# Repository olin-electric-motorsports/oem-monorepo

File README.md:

<h1 align="center">
	
</h1>

Welcome to the Olin Electric Motorsports monorepo. This is the home for all of our
electrical, firmware, and software work.

This document will help you get started contributing and walk you through
important steps for working on the team.

## Getting Started

If you are on a completely fresh Ubuntu computer, you won't have the tools needed to download this repository yet. Open your terminal (`Ctrl` + `Alt` + `T`) and run these commands one by one to install Git and clone our code:

**1. Install Git:**
```shell
sudo apt update
sudo apt install git -y
git clone https://github.com/olin-electric-motorsports/oem-monorepo oem-monorepo
cd oem-monorepo
```
Now we need to install a few things so lets run. 
```shell
./scripts/startup/quick-setup.sh
```

Go through this and install the packages

## Repository Configuration

Once your system has all the required packages, you need to configure your local repository settings to keep our KiCad libraries clean.
*   Run the KiCad Git filters script to apply rules that remove temporary files and prevent clutter:
    `./scripts/startup/install_kicad_git_filters.sh`
*   Run the KiCad Git Hooks script to install Git LFS and the hooks required to generate our symbol libraries on every push/pull:
    `./scripts/startup/install_kicad_git_hooks.sh`

## Testing Your Setup

Verify that your system is ready by running the following commands in your terminal:
*   Check your Bazel installation: `bazel version`
*   Check your OpenOCD installation: `openocd --version`
*   Test the vehicle firmware build: `bazel build //vehicle/... --config=m4`

If the final command outputs a lot of green text, your environment is perfectly configured!

## Firmware Workflow

Here are the standard Bazel commands you will use to interact with the STM32 microcontrollers. 

**Building specific targets (creates the .elf file):**
`bazel build --config=m4 //vehicle/examples/blinky:blinky.elf`

**Initializing new chips (configures the boot pin on fresh silicon):**
`bazel run --config=m4 //vehicle/examples/blinky:blinky_initialize`

**Flashing firmware using the ST-Link:**
`bazel run --config=m4 //vehicle/examples/blinky:blinky_flash`

**Debugging using OpenOCD and GDB:**
`bazel run -c dbg --config=m4 //vehicle/examples/blinky:blinky_debug`

## Contributing: Branches and Pull Requests

To keep our codebase stable and functional, we do not push code directly to the `main` branch. Instead, we use branches and Pull Requests (PRs) so code can be reviewed before it is merged. Here is the standard workflow for contributing:

**1. Get the Latest Code**
Always start by making sure your local repository is up-to-date with everyone else's work:
```shell
git checkout main
git pull origin main
```

**2. Create a New Branch**
Create a new branch for your specific feature or fix. Use a descriptive name and your name so the team knows what you are working on (e.g., `CoolerJacob/blinky-led`, `Jelly_Kelly/adc-reading`):
```shell
git checkout -b your-branch-name
```

**3. Make Your Changes and Commit**
Write your code, verify it builds, and then stage and commit your changes with a clear, descriptive message:
```shell
git add .
git commit -m "Brief description of what you changed and why"
```

**4. Push Your Branch**
Upload your newly created branch to the remote repository so the team can see it:
```shell
git push -u origin your-branch-name
```

**5. Open a Pull Request (PR)**
*   Go to our repository in your web browser.
*   You will usually see a green prompt saying "Compare & pull request" for your recently pushed branch.
*   Click it, fill out a description of what your code does, and submit the PR.
*   Tag a teammate to review your code. Once it is approved, you can merge it into `main`!

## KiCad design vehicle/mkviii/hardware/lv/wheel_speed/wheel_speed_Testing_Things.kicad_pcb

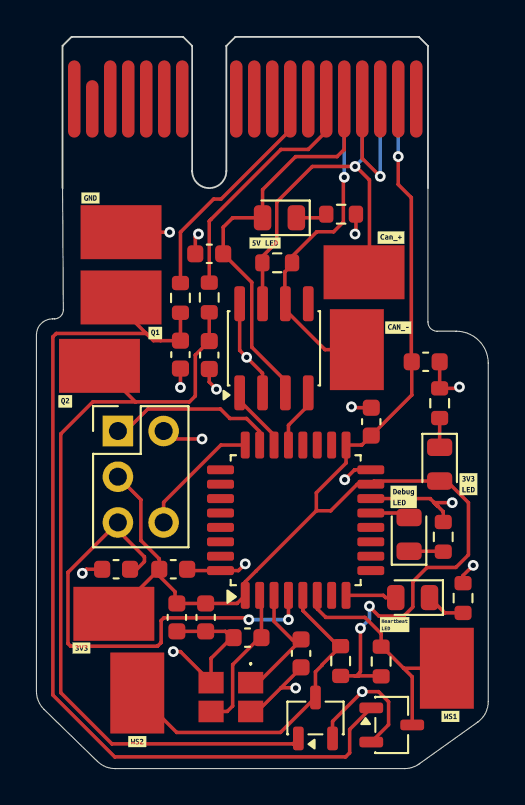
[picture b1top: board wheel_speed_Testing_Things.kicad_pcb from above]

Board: 2 copper layers, 25.1 x 40.6 mm, 51 parts (0 on the bottom side), 24 nets.

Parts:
C1, C10, C11: C_10nF; C_0603_1608Metric
C2, C3, C5, C8: C_0.1uF; C_0603_1608Metric
C4: C_1uF; C_0603_1608Metric
C6: C_4.7uF; C_0603_1608Metric
C7, C9: C_30pF; C_0603_1608Metric
Can_Testpoint1, Can_Testpoint2: TestPoint; TP_Hook_SMD
D1, D2, D3, D4: D_Blue_LED; D_0805_2012Metric
GND1: TestPoint; TP_Hook_SMD
J1: J_Programming_Pin_Header; J_Programming_Pin_Header_Keyed
J2: J_PCIe_x1; J_PCIe_x1_Key
Q1, Q2: SSM3K333R,LF; SOT-23-3
R1: R_120; R_0603_1608Metric
R2, R3, R4, R5, R7, R8, R10, R11: R_1k; R_0603_1608Metric
U1: MCP2561-E-SN; SOIC-8_3.9x4.9mm_P1.27mm
U2: STM32G441KBT6; LQFP-32_7x7mm_P0.8mm
VDD1: TestPoint; TP_Hook_SMD
WS1_Output1, WS1_Output2, WS2_Output1, WS2_Output2: TestPoint; TP_Hook_SMD
X1: X_16MHz_18pF; FA238160000MBC0 (X_16MHz_18pF_SMD - FA-238_16.0000MB-C0)
kibuzzard-6AF66A6A: G***; kibuzzard-6AF66A6A
kibuzzard-6AF66B68: G***; kibuzzard-6AF66B68
kibuzzard-6AF66B73: G***; kibuzzard-6AF66B73
kibuzzard-6AF667D2: G***; kibuzzard-6AF667D2
kibuzzard-6AF667FB: G***; kibuzzard-6AF667FB
kibuzzard-6AF6682B: G***; kibuzzard-6AF6682B
kibuzzard-6AF6683B: G***; kibuzzard-6AF6683B
kibuzzard-6AF6685D: G***; kibuzzard-6AF6685D
kibuzzard-6AF66808: G***; kibuzzard-6AF66808
kibuzzard-6AF66816: G***; kibuzzard-6AF66816
kibuzzard-6AF66821: G***; kibuzzard-6AF66821
kibuzzard-6AF66851: G***; kibuzzard-6AF66851

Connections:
+3V3: C1.1, C2.1, C3.1, C4.1, C6.1, D4.2 (A), J1.3, J2.A2 (12V/3V(DA_ONLY)), R7.1, R8.1, U2.1 (VDD), U2.15 (VDDA), U2.17 (VDD), VDD1.1
+5V: C5.2, D3.2 (A), J2.B5 (5V), U1.3 (VDD)
/CAN_+: Can_Testpoint1.1, J2.A4 (CAN+), R1.1, U1.7 (CANH)
/CAN_-: Can_Testpoint2.1, J2.A5 (CAN-), R1.2, U1.6 (CANL)
/CAN_RX: U1.4 (RXD), U2.21 ((EVENTOUT/TIM1_BKIN2/TIM1_CH4/TIM4_CH1/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)
/CAN_TX: U1.1 (TXD), U2.22 ((EVENTOUT/TIM1_ETR/TIM4_CH2/FDCAN1_TX/C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)
/DEBUG_LED: D1.2 (A), U2.13 ((EVENTOUT/UCPD1_FRSTX2/UCPD_FRSTX1/TIM1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)
/HEARTBEAT_LED: D2.2 (A), U2.8 ((EVENTOUT/SAI1_MCLK_A/LPUART1_RX/TIM15_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)
/NRST: C8.1, J1.4, U2.4 ((EVENTOUT/RCC_MCO/GPIO_EXTI10)PG10-NRST)
/SWCLK: J1.5, U2.24 ((EVENTOUT/SAI1_FS_B/USART2_TX/TIM1_BKIN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)
/SWDIO: J1.1, U2.23 ((EVENTOUT/SAI1_SD_B/TIM4_CH3/IR_OUT/I2C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)
/ws1_Vout: J2.B8 (io_5), R4.1
/ws1_fVout: Q1.3 (D), R8.2, U2.6 ((EVENTOUT/TIM15_CH1N/USART2_RTS/USART2_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), WS1_Output1.1
/ws2_Vout: J2.B6 (io_1), R5.1
/ws2_fVout: Q2.3 (D), R7.2, U2.5 ((EVENTOUT/TIM2_ETR/TIM8_ETR/TIM8_BKIN/C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), WS2_Output1.1
GND: C1.2, C2.2, C3.2, C4.2, C5.1, C6.2, C7.2, C8.2, C9.2, C10.2, C11.2, GND1.1, J1.2, J2.A3 (GND), J2.B4 (GND), Q1.2 (S), Q2.2 (S), R2.1, R3.1, R10.1, R11.1, U1.2 (VSS), U1.8 (STBY), U2.14 (VSSA), U2.16 (VSS), U2.32 (VSS), X1.2, X1.4
unnamed: D1.1 (K), R2.2
unnamed: D2.1 (K), R3.2
unnamed: D3.1 (K), R10.2
unnamed: D4.1 (K), R11.2
unnamed: C10.1, Q1.1 (G), R4.2, WS1_Output2.1
unnamed: C11.1, Q2.1 (G), R5.2, WS2_Output2.1
unnamed: C7.1, U2.3 ((EVENTOUT/SPI2_SCK)PF1-OSC_OUT), X1.1
unnamed: C9.1, U2.2 ((EVENTOUT/TIM1_CH3N/SPI2_NSS/I2C2_WS/I2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), X1.3

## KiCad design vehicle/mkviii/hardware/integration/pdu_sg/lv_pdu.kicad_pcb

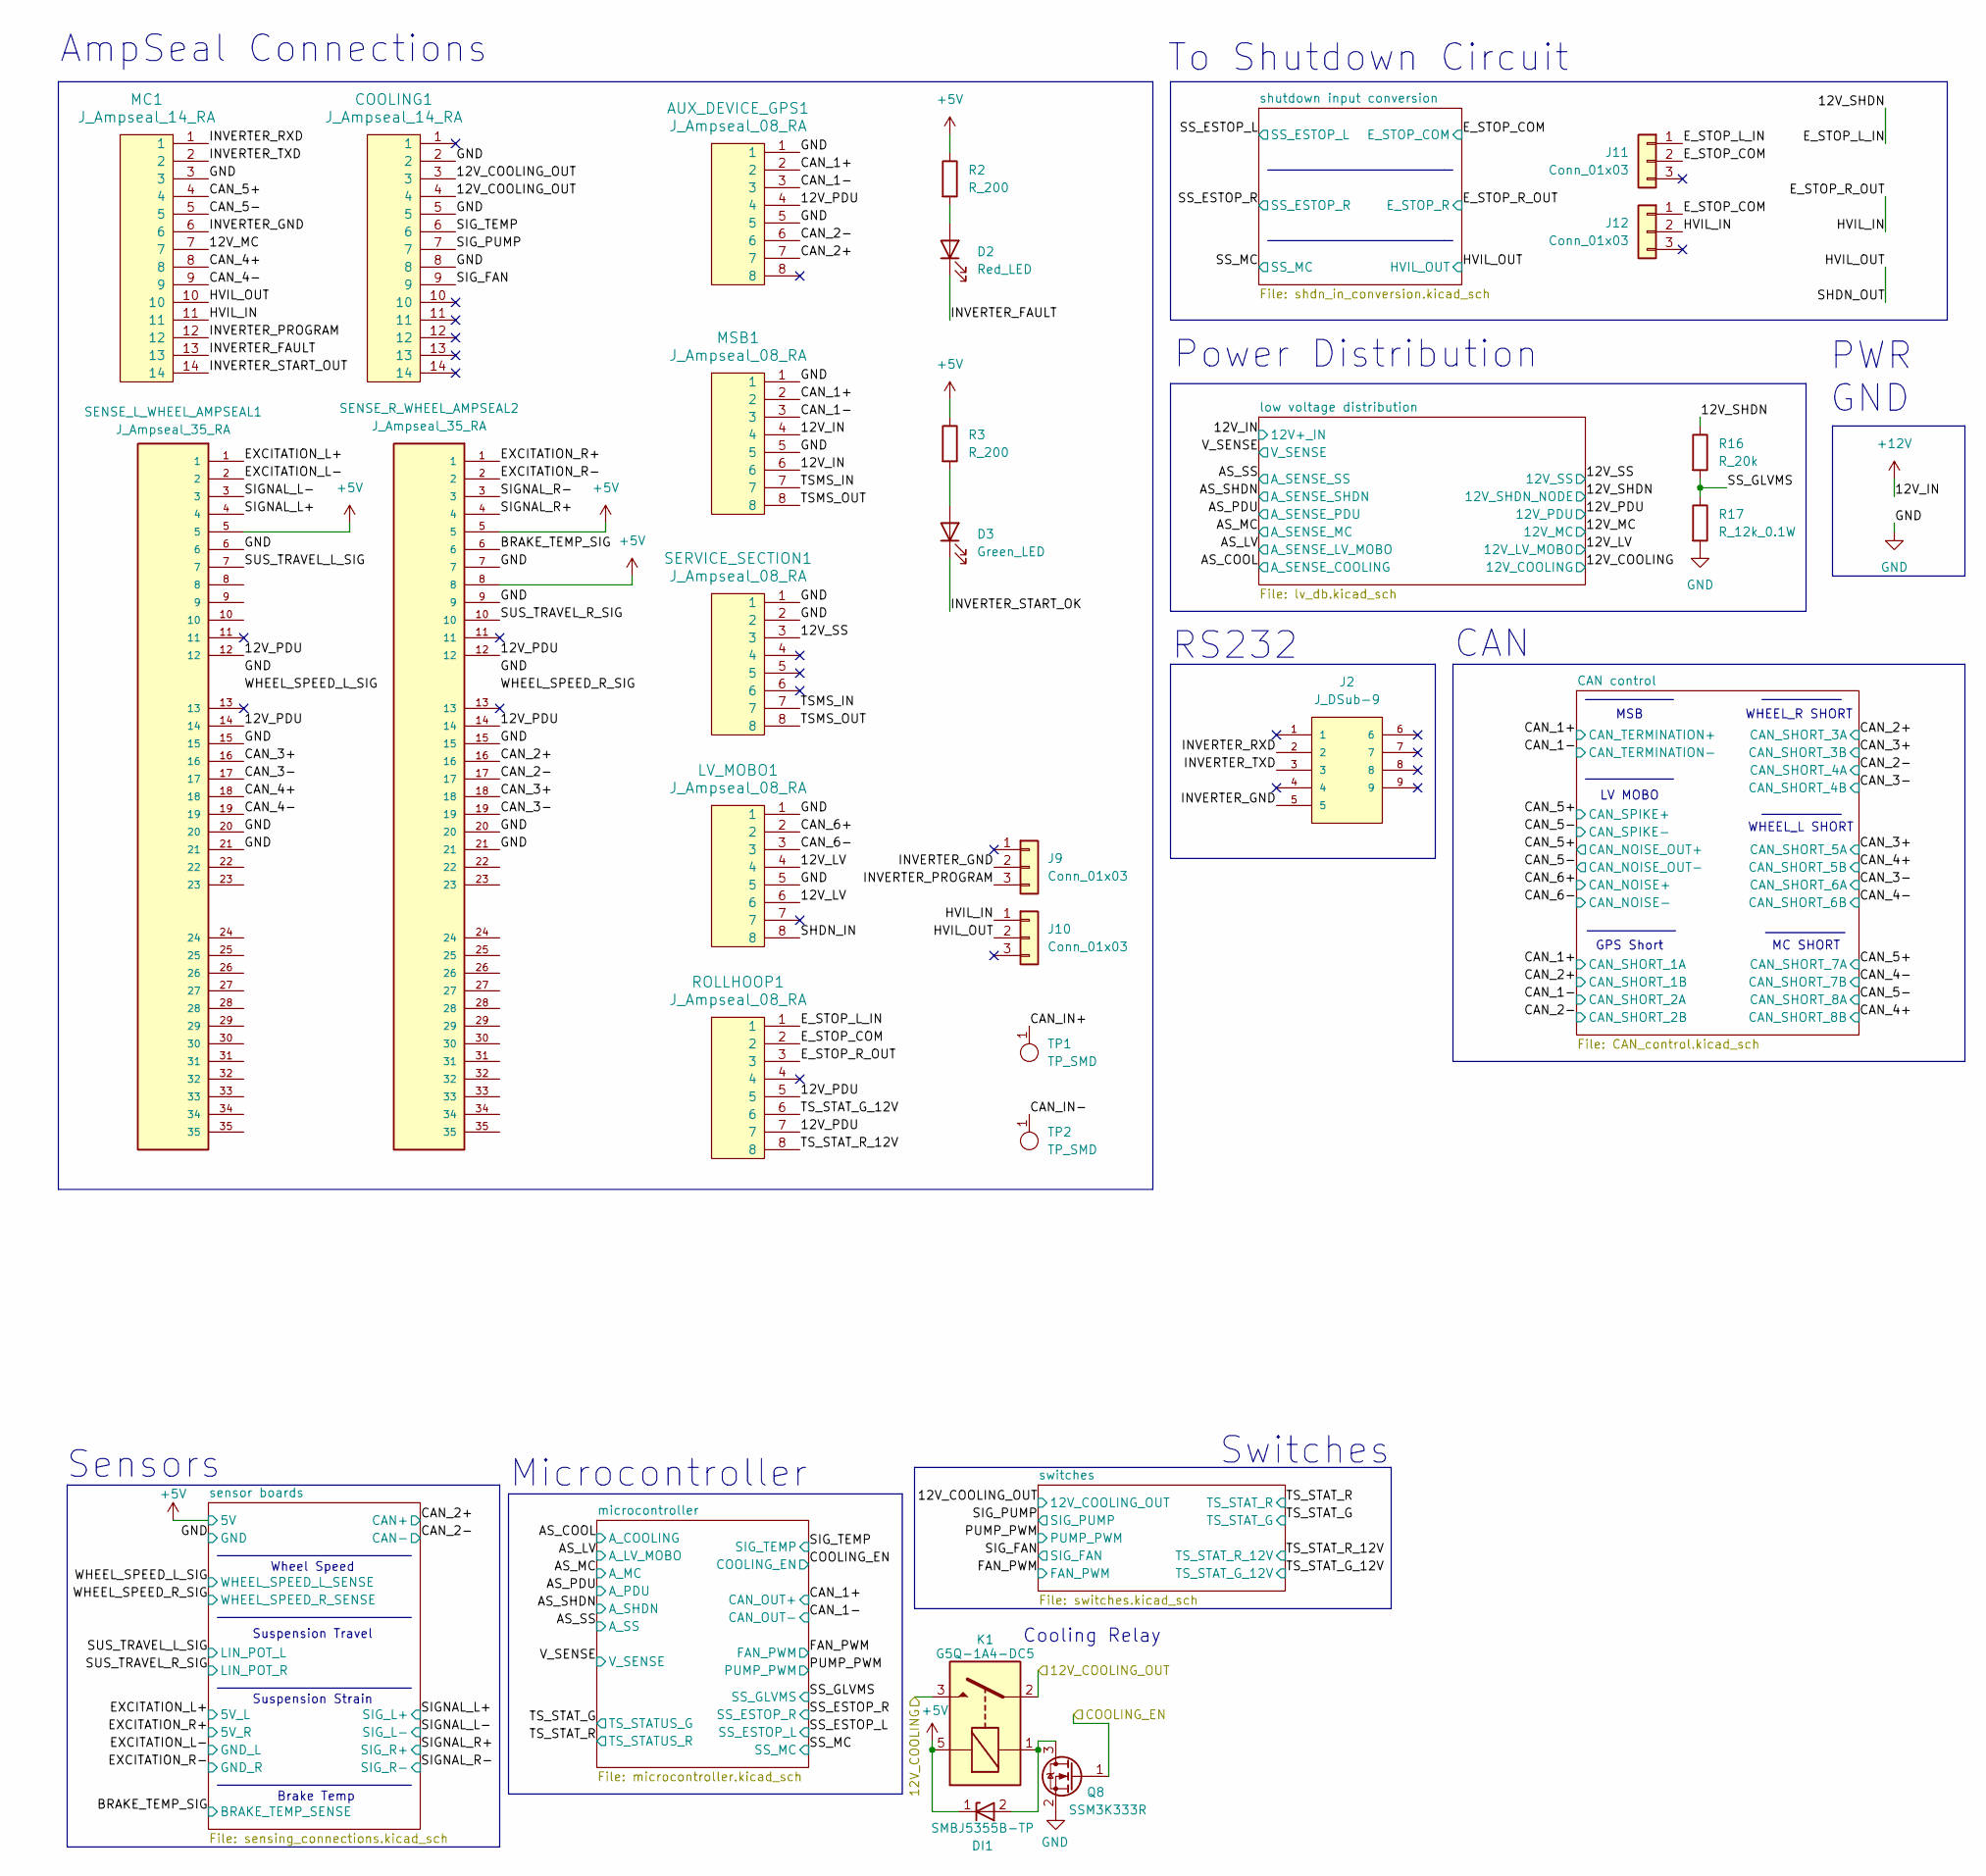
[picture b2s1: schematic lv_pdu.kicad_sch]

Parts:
AUX_DEVICE_GPS1: J_Ampseal_08_RA; J_Ampseal_8_RA; MPN 1-776279-1
COOLING1: J_Ampseal_14_RA; MPN 1-776266-1
D2: Red_LED; D_0805_2012Metric; MPN LTST-C171KRKT
D3: Green_LED; D_0805_2012Metric; MPN LTST-C170KGKT
DI1: SMBJ5355B-TP; D_Zener_18V_5W_DO214AA - DIOM5336X262N; MPN SMBJ5355B-TP
J2: J_DSub-9; J_DE-9_RA; MPN 5745781-4
J9, J10, J11, J12: Conn_01x03; PinHeader_1x03_P2.54mm_Vertical
K1: G5Q-1A4-DC5; G5Q1A4DC24 (K_SPST-NO_10A_12V_TH - G5Q-1A4-DC12); MPN G5Q-1A4 DC5
LV_MOBO1: J_Ampseal_08_RA; J_Ampseal_8_RA; MPN 1-776279-1
MC1: J_Ampseal_14_RA; MPN 1-776266-1
MSB1: J_Ampseal_08_RA; J_Ampseal_8_RA; MPN 1-776279-1
Q8: SSM3K333R; SOT-23-3; MPN SSM3K333R,LF
R2, R3: R_200; R_0603_1608Metric; MPN WR06X2000FTL
R16: R_20k; R_2512_6332Metric; MPN SR2512JK-7W20KL
R17: R_12k_0.1W; R_0603_1608Metric; MPN RMCF0603FT12K0
ROLLHOOP1: J_Ampseal_08_RA; J_Ampseal_8_RA; MPN 1-776279-1
SENSE_L_WHEEL_AMPSEAL1: J_Ampseal_35_RA; VOLTAGE_RATING 250VAC; MPN 1-776163-4
SENSE_R_WHEEL_AMPSEAL2: J_Ampseal_35_RA; VOLTAGE_RATING 250VAC; MPN 1-776163-4
SERVICE_SECTION1: J_Ampseal_08_RA; J_Ampseal_8_RA; MPN 1-776279-1
TP1, TP2: TP_SMD; TP_Hook_SMD; MPN 5019

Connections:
+5V: DI1.1 (K), K1.5, R2.1, R3.1, SENSE_L_WHEEL_AMPSEAL1.5, SENSE_R_WHEEL_AMPSEAL2.5, SENSE_R_WHEEL_AMPSEAL2.8; also elsewhere on the board
+12V: MSB1.4, MSB1.6; also elsewhere on the board
/12V_COOLING: K1.3; also elsewhere on the board
/12V_COOLING_OUT: COOLING1.3, COOLING1.4, K1.2; also elsewhere on the board
/12V_LV: LV_MOBO1.4, LV_MOBO1.6; also elsewhere on the board
/12V_MC: MC1.7; also elsewhere on the board
/12V_SHDN: J11.1, R16.1, ROLLHOOP1.1; also elsewhere on the board
/12V_SS: SERVICE_SECTION1.3; also elsewhere on the board
/BRAKE_TEMP_SIG: SENSE_R_WHEEL_AMPSEAL2.6; also elsewhere on the board
/CAN_1+: AUX_DEVICE_GPS1.2, MSB1.2; also elsewhere on the board
/CAN_1-: AUX_DEVICE_GPS1.3, MSB1.3; also elsewhere on the board
/CAN_2+: AUX_DEVICE_GPS1.7, SENSE_R_WHEEL_AMPSEAL2.16; also elsewhere on the board
/CAN_2-: AUX_DEVICE_GPS1.6, SENSE_R_WHEEL_AMPSEAL2.17; also elsewhere on the board
/CAN_3+: SENSE_L_WHEEL_AMPSEAL1.16, SENSE_R_WHEEL_AMPSEAL2.18; also elsewhere on the board
/CAN_3-: SENSE_L_WHEEL_AMPSEAL1.17, SENSE_R_WHEEL_AMPSEAL2.19; also elsewhere on the board
/CAN_4+: MC1.8, SENSE_L_WHEEL_AMPSEAL1.18; also elsewhere on the board
/CAN_4-: MC1.9, SENSE_L_WHEEL_AMPSEAL1.19; also elsewhere on the board
/CAN_5+: MC1.4; also elsewhere on the board
/CAN_5-: MC1.5; also elsewhere on the board
/CAN_6+: LV_MOBO1.2; also elsewhere on the board
/CAN_6-: LV_MOBO1.3; also elsewhere on the board
/CAN_IN+: TP1.1
/CAN_IN-: TP2.1
/COOLING_EN: Q8.1 (G); also elsewhere on the board
/EXCITATION_L+: SENSE_L_WHEEL_AMPSEAL1.1; also elsewhere on the board
/EXCITATION_L-: SENSE_L_WHEEL_AMPSEAL1.2; also elsewhere on the board
/EXCITATION_R+: SENSE_R_WHEEL_AMPSEAL2.1; also elsewhere on the board
/EXCITATION_R-: SENSE_R_WHEEL_AMPSEAL2.2; also elsewhere on the board
/E_STOP_COM: J11.2, J12.1, ROLLHOOP1.2; also elsewhere on the board
/E_STOP_R_OUT: J10.1, J12.2, MC1.11, ROLLHOOP1.3; also elsewhere on the board
/HVIL_OUT: J10.2, MC1.10; also elsewhere on the board
/INVERTER_FAULT: D2.1 (K), MC1.13
/INVERTER_GND: J2.5, J9.2, MC1.6
/INVERTER_PROGRAM: J9.3, MC1.12
/INVERTER_RXD: J2.2, MC1.1
/INVERTER_START_OK: D3.1 (K)
/INVERTER_START_OUT: MC1.14
/INVERTER_TXD: J2.3, MC1.2
/SHDN_IN: LV_MOBO1.8
/SIGNAL_L+: SENSE_L_WHEEL_AMPSEAL1.4; also elsewhere on the board
/SIGNAL_L-: SENSE_L_WHEEL_AMPSEAL1.3; also elsewhere on the board
/SIGNAL_R+: SENSE_R_WHEEL_AMPSEAL2.4; also elsewhere on the board
/SIGNAL_R-: SENSE_R_WHEEL_AMPSEAL2.3; also elsewhere on the board
/SIG_FAN: COOLING1.9; also elsewhere on the board
/SIG_PUMP: COOLING1.7; also elsewhere on the board
/SIG_TEMP: COOLING1.6; also elsewhere on the board
/SS_GLVMS: R16.2, R17.1; also elsewhere on the board
/SUS_TRAVEL_L_SIG: SENSE_L_WHEEL_AMPSEAL1.7; also elsewhere on the board
/SUS_TRAVEL_R_SIG: SENSE_R_WHEEL_AMPSEAL2.10; also elsewhere on the board
/TSMS_IN: MSB1.7, SERVICE_SECTION1.7
/TSMS_OUT: MSB1.8, SERVICE_SECTION1.8
/TS_STAT_G_12V: ROLLHOOP1.6; also elsewhere on the board
/TS_STAT_R_12V: ROLLHOOP1.8; also elsewhere on the board
GND: AUX_DEVICE_GPS1.1, AUX_DEVICE_GPS1.5, COOLING1.2, COOLING1.5, COOLING1.8, LV_MOBO1.1, LV_MOBO1.5, MC1.3, MSB1.1, MSB1.5, Q8.2 (S), R17.2, SENSE_L_WHEEL_AMPSEAL1.6, SENSE_L_WHEEL_AMPSEAL1.15, SENSE_L_WHEEL_AMPSEAL1.20, SENSE_L_WHEEL_AMPSEAL1.21, SENSE_R_WHEEL_AMPSEAL2.7, SENSE_R_WHEEL_AMPSEAL2.9, SENSE_R_WHEEL_AMPSEAL2.15, SENSE_R_WHEEL_AMPSEAL2.20, SENSE_R_WHEEL_AMPSEAL2.21, SERVICE_SECTION1.1, SERVICE_SECTION1.2; also elsewhere on the board
unnamed: D2.2 (A), R2.2
unnamed: D3.2 (A), R3.2
unnamed: DI1.2 (A), K1.1, Q8.3 (D)

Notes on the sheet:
Wheel Speed
Sensors
Switches
Suspension Travel
Power Distribution
GPS Short
Microcontroller
MSB
MC SHORT
CAN
WHEEL_R SHORT
RS232
Cooling Relay
To Shutdown Circuit
WHEEL_L SHORT
Suspension Strain
AmpSeal Connections
Brake Temp
PWR GND
LV MOBO

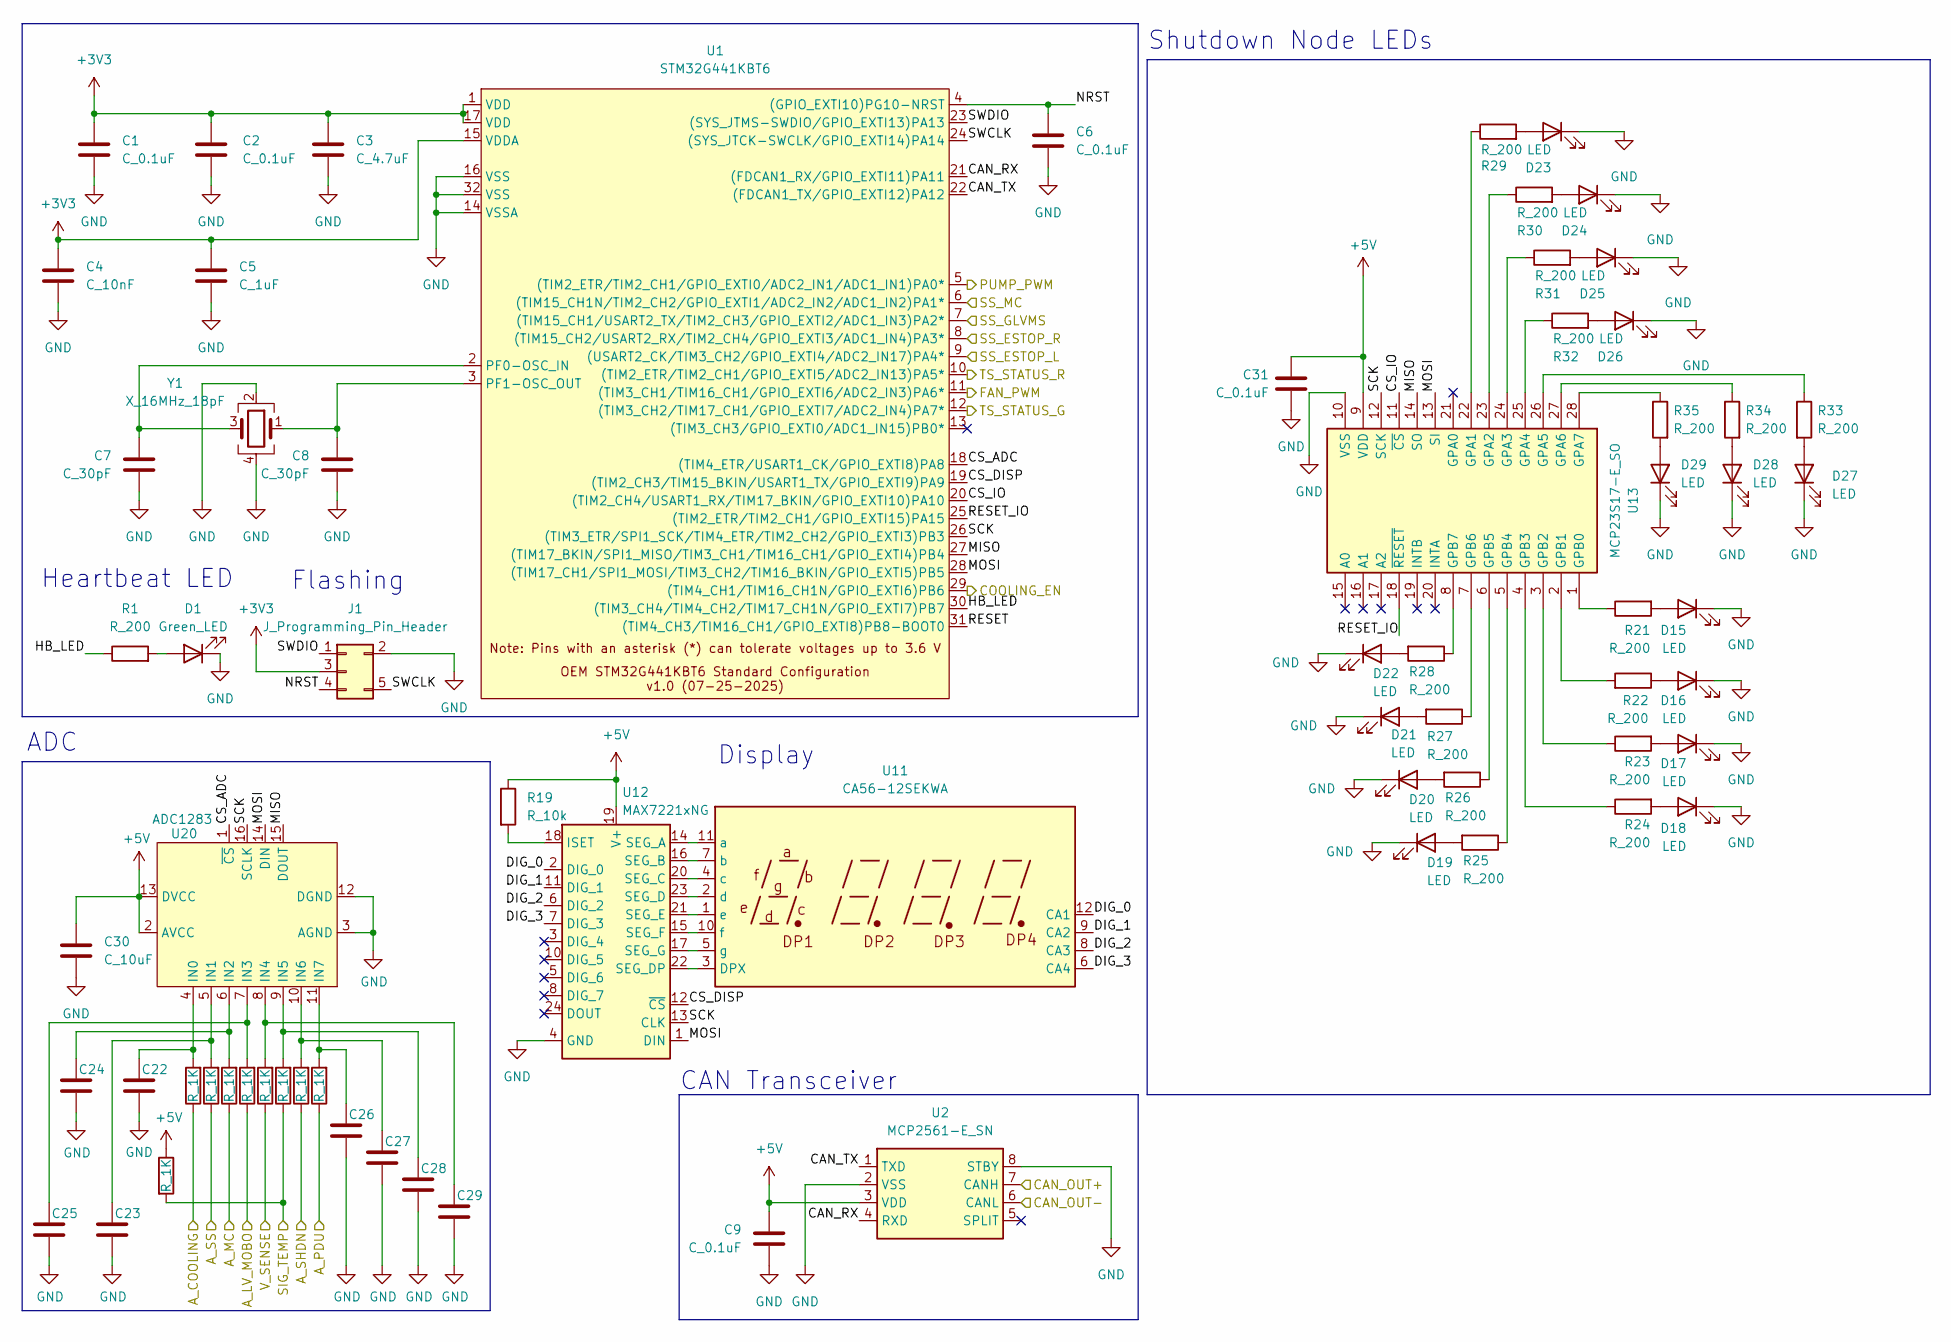
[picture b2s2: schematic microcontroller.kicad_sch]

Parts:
C1, C2, C6, C9: C_0.1uF; C_0603_1608Metric; MPN CL10B104KB8NNWC
C3: C_4.7uF; C_0603_1608Metric; MPN GRT188R61E475ME13D
C4: C_10nF; C_0603_1608Metric; MPN CL10B103KB8NNNC
C5: C_1uF; C_0603_1608Metric; MPN CL10B105KA8NNNC
C7, C8: C_30pF; C_0603_1608Metric; MPN CML0603C0G300JT50V
C22, C23, C24, C25, C26, C27, C28, C29: C_10uF; C_0603_1608Metric; MPN LMK107BBJ106KALT
C30: C_10uF; C_0603_1608Metric; MPN GRM188D71A106KA73D
C31: C_0.1uF; C_0603_1608Metric; MPN C0603C104Z4VACTU
D1: Green_LED; D_0805_2012Metric; MPN LTST-C170KGKT
D15, D16, D17, D18, D19, D20, D21, D22, D23, D24, D25, D26, D27, D28, D29: LED; D_0805_2012Metric; MPN QBLP631-IW
J1: J_Programming_Pin_Header; J_Programming_Pin_Header_Keyed
R1, R21, R22, R23, R24, R25, R26, R27, R28, R29, R30, R31, R32, R33, R34, R35: R_200; R_0603_1608Metric; MPN WR06X2000FTL
R18, R20, R45, R54, R55, R56, R57, R58, R59: R_1K; R_0603_1608Metric; MPN RMCF0603FT1K00
R19: R_10k; R_0603_1608Metric; MPN RMCF0603FT10K0
U1: STM32G441KBT6; LQFP-32_7x7mm_P0.8mm
U2: MCP2561-E_SN; SOIC-8_3.9x4.9mm_P1.27mm; MPN MCP2561-E/SN
U11: CA56-12SEKWA
U12: MAX7221xNG; DIP-24_W7.62mm
U13: MCP23S17-E_SO; U_SPI-IO-Xpndr_MCP23S17-E_SO_SOIC-28; MPN MCP23S17-E/SO
U20: ADC1283; TSSOP-16_4.4x5mm_P0.65mm
Y1: X_16MHz_18pF; FA238160000MBC0 (X_16MHz_18pF_SMD - FA-238_16.0000MB-C0); MPN FA-238 16.0000MB-C0

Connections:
+3V3: C1.1, C2.1, C3.1, C4.1, C5.1, J1.3, U1.1 (VDD), U1.15 (VDDA), U1.17 (VDD)
+5V: C9.1, C30.1, C31.1, R19.1, R45.1, U2.3 (VDD), U12.19 (V+), U13.9 (VDD), U20.2 (AVCC), U20.13 (DVCC); also elsewhere on the board
/AS_COOL: R18.1; also elsewhere on the board
/AS_LV: R55.1; also elsewhere on the board
/AS_MC: R54.1; also elsewhere on the board
/AS_PDU: R59.1; also elsewhere on the board
/AS_SHDN: R58.1; also elsewhere on the board
/AS_SS: R20.1; also elsewhere on the board
/CAN_1+: U2.7 (CANH); also elsewhere on the board
/CAN_1-: U2.6 (CANL); also elsewhere on the board
/COOLING_EN: U1.29 ((TIM4_CH1/TIM16_CH1N/GPIO_EXTI6)PB6); also elsewhere on the board
/FAN_PWM: U1.11 ((TIM3_CH1/TIM16_CH1/GPIO_EXTI6/ADC2_IN3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); also elsewhere on the board
/PUMP_PWM: U1.5 ((TIM2_ETR/TIM2_CH1/GPIO_EXTI0/ADC2_IN1/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); also elsewhere on the board
/SIG_TEMP: R45.2, R57.1; also elsewhere on the board
/SS_ESTOP_L: U1.9 ((USART2_CK/TIM3_CH2/GPIO_EXTI4/ADC2_IN1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); also elsewhere on the board
/SS_ESTOP_R: U1.8 ((TIM15_CH2/USART2_RX/TIM2_CH4/GPIO_EXTI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); also elsewhere on the board
/SS_GLVMS: U1.7 ((TIM15_CH1/USART2_TX/TIM2_CH3/GPIO_EXTI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); also elsewhere on the board
/SS_MC: U1.6 ((TIM15_CH1N/TIM2_CH2/GPIO_EXTI1/ADC2_IN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); also elsewhere on the board
/TS_STAT_G: U1.12 ((TIM3_CH2/TIM17_CH1/GPIO_EXTI7/ADC2_IN4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); also elsewhere on the board
/TS_STAT_R: U1.10 ((TIM2_ETR/TIM2_CH1/GPIO_EXTI5/ADC2_IN13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); also elsewhere on the board
/V_SENSE: R56.1; also elsewhere on the board
/microcontroller/CAN_RX: U1.21 ((FDCAN1_RX/GPIO_EXTI11)PA11), U2.4 (RXD)
/microcontroller/CAN_TX: U1.22 ((FDCAN1_TX/GPIO_EXTI12)PA12), U2.1 (TXD)
/microcontroller/CS_ADC: U1.18 ((TIM4_ETR/USART1_CK/GPIO_EXTI8)PA8), U20.1 (~CS)
/microcontroller/CS_DISP: U1.19 ((TIM2_CH3/TIM15_BKIN/USART1_TX/GPIO_EXT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), U12.12 (~CS)
/microcontroller/CS_IO: U1.20 ((TIM2_CH4/USART1_RX/TIM17_BKIN/GPIO_EXT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), U13.11 (~CS)
/microcontroller/DIG_0: U11.12 (CA1), U12.2 (DIG_0)
/microcontroller/DIG_1: U11.9 (CA2), U12.11 (DIG_1)
/microcontroller/DIG_2: U11.8 (CA3), U12.6 (DIG_2)
/microcontroller/DIG_3: U11.6 (CA4), U12.7 (DIG_3)
/microcontroller/HB_LED: R1.1, U1.30 ((TIM3_CH4/TIM4_CH2/TIM17_CH1N/GPIO_EXTI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)
/microcontroller/MISO: U1.27 ((TIM17_BKIN/SPI1_MISO/TIM3_CH1/TIM16_CH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), U13.14 (SO), U20.15 (DOUT)
/microcontroller/MOSI: U1.28 ((TIM17_CH1/SPI1_MOSI/TIM3_CH2/TIM16_BKI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), U12.1 (DIN), U13.13 (SI), U20.14 (DIN)
/microcontroller/NRST: C6.1, J1.4, U1.4 ((GPIO_EXTI10)PG10-NRST)
/microcontroller/RESET: U1.31 ((TIM4_CH3/TIM16_CH1/GPIO_EXTI8)PB8-BOOT0)
/microcontroller/RESET_IO: U1.25 ((TIM2_ETR/TIM2_CH1/GPIO_EXTI15)PA15), U13.18 (~RESET)
/microcontroller/SCK: U1.26 ((TIM3_ETR/SPI1_SCK/TIM4_ETR/TIM2_CH2/GP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), U12.13 (CLK), U13.12 (SCK), U20.16 (SCLK)
/microcontroller/SWCLK: J1.5, U1.24 ((SYS_JTCK-SWCLK/GPIO_EXTI14)PA14)
/microcontroller/SWDIO: J1.1, U1.23 ((SYS_JTMS-SWDIO/GPIO_EXTI13)PA13)
GND: C1.2, C2.2, C3.2, C4.2, C5.2, C6.2, C7.2, C8.2, C9.2, C22.2, C23.2, C24.2, C25.2, C26.2, C27.2, C28.2, C29.2, C30.2, C31.2, D1.1 (K), D15.1 (K), D16.1 (K), D17.1 (K), D18.1 (K), D19.1 (K), D20.1 (K), D21.1 (K), D22.1 (K), D23.1 (K), D24.1 (K), D25.1 (K), D26.1 (K), D27.1 (K), D28.1 (K), D29.1 (K), J1.2, U1.14 (VSSA), U1.16 (VSS), U1.32 (VSS), U2.2 (VSS), U2.8 (STBY), U12.4 (GND), U13.10 (VSS), U20.3 (AGND), U20.12 (DGND), Y1.2, Y1.4; also elsewhere on the board
unnamed: D1.2 (A), R1.2
unnamed: D15.2 (A), R21.2
unnamed: D16.2 (A), R22.1
unnamed: D17.2 (A), R23.2
unnamed: D18.2 (A), R24.2
unnamed: D19.2 (A), R25.2
unnamed: D20.2 (A), R26.2
unnamed: D21.2 (A), R27.2
unnamed: D22.2 (A), R28.2
unnamed: D23.2 (A), R29.2
unnamed: D24.2 (A), R30.2
unnamed: D25.2 (A), R31.2
unnamed: D26.2 (A), R32.2
unnamed: D27.2 (A), R33.2
unnamed: D28.2 (A), R34.2
unnamed: D29.2 (A), R35.2
unnamed: C7.1, U1.2 (PF0-OSC_IN), Y1.3
unnamed: C8.1, U1.3 (PF1-OSC_OUT), Y1.1
unnamed: U11.3 (DPX), U12.22 (SEG_DP)
unnamed: U11.11 (a), U12.14 (SEG_A)
unnamed: U11.7 (b), U12.16 (SEG_B)
unnamed: U11.4 (c), U12.20 (SEG_C)
unnamed: U11.2 (d), U12.23 (SEG_D)
unnamed: U11.1 (e), U12.21 (SEG_E)
unnamed: U11.10 (f), U12.15 (SEG_F)
unnamed: U11.5 (g), U12.17 (SEG_G)
unnamed: R19.2, U12.18 (ISET)
unnamed: R29.1, U13.22 (GPA1)
unnamed: R30.1, U13.23 (GPA2)
unnamed: R31.1, U13.24 (GPA3)
unnamed: R32.1, U13.25 (GPA4)
unnamed: R33.1, U13.26 (GPA5)
unnamed: R34.1, U13.27 (GPA6)
unnamed: R35.1, U13.28 (GPA7)
unnamed: R21.1, U13.1 (GPB0)
unnamed: R22.2, U13.2 (GPB1)
unnamed: R23.1, U13.3 (GPB2)
unnamed: R24.1, U13.4 (GPB3)
unnamed: R25.1, U13.5 (GPB4)
unnamed: R26.1, U13.6 (GPB5)
unnamed: R27.1, U13.7 (GPB6)
unnamed: R28.1, U13.8 (GPB7)
unnamed: C22.1, R18.2, U20.4 (IN0)
unnamed: C23.1, R20.2, U20.5 (IN1)
unnamed: C24.1, R54.2, U20.6 (IN2)
unnamed: C25.1, R55.2, U20.7 (IN3)
unnamed: C29.1, R56.2, U20.8 (IN4)
unnamed: C28.1, R57.2, U20.9 (IN5)
unnamed: C27.1, R58.2, U20.10 (IN6)
unnamed: C26.1, R59.2, U20.11 (IN7)

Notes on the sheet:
Heartbeat LED
ADC
Flashing
CAN Transceiver
Display
Shutdown Node LEDs

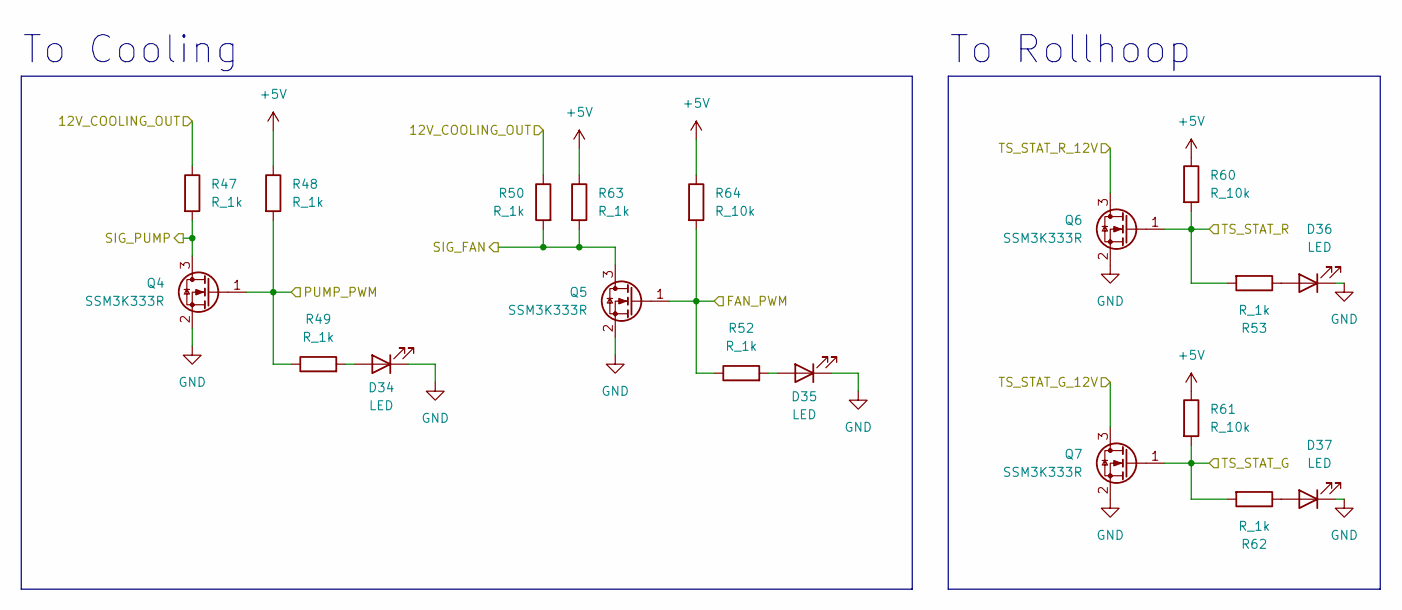
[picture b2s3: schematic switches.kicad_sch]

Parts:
D34, D35, D36, D37: LED; D_0805_2012Metric; MPN QBLP631-IW
Q4, Q5, Q6, Q7: SSM3K333R; SOT-23-3
R47, R48, R49, R50, R52, R53, R62, R63: R_1k; R_0603_1608Metric; MPN RMCF0603FT1K00 (or ERJ-3GEYJ102V)
R60, R61, R64: R_10k; R_0603_1608Metric; MPN RMCF0603FT10K0

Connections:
+5V: R48.1, R60.1, R61.1, R63.1, R64.1; also elsewhere on the board
/12V_COOLING_OUT: R47.1, R50.1; also elsewhere on the board
/FAN_PWM: Q5.1 (G), R52.1, R64.2; also elsewhere on the board
/PUMP_PWM: Q4.1 (G), R48.2, R49.1; also elsewhere on the board
/SIG_FAN: Q5.3 (D), R50.2, R63.2; also elsewhere on the board
/SIG_PUMP: Q4.3 (D), R47.2; also elsewhere on the board
/TS_STAT_G: Q7.1 (G), R61.2, R62.2; also elsewhere on the board
/TS_STAT_G_12V: Q7.3 (D); also elsewhere on the board
/TS_STAT_R: Q6.1 (G), R53.2, R60.2; also elsewhere on the board
/TS_STAT_R_12V: Q6.3 (D); also elsewhere on the board
GND: D34.1 (K), D35.1 (K), D36.1 (K), D37.1 (K), Q4.2 (S), Q5.2 (S), Q6.2 (S), Q7.2 (S); also elsewhere on the board
unnamed: D34.2 (A), R49.2
unnamed: D35.2 (A), R52.2
unnamed: D36.2 (A), R53.1
unnamed: D37.2 (A), R62.1

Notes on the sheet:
To Rollhoop
To Cooling

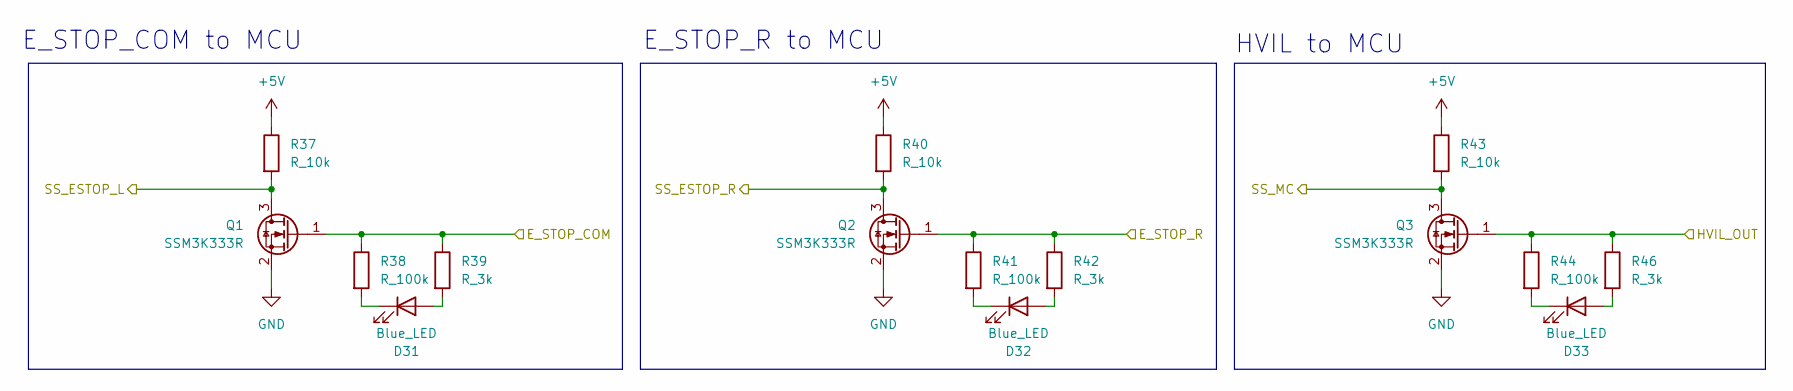
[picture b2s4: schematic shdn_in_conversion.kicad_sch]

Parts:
D31, D32, D33: Blue_LED; D_0805_2012Metric; MPN LTST-C171TBKT
Q1, Q2, Q3: SSM3K333R; SOT-23-3
R37, R40, R43: R_10k; R_0603_1608Metric; MPN RMCF0603FT10K0
R38, R41, R44: R_100k; R_0603_1608Metric; MPN RMCF0603FT100K
R39, R42, R46: R_3k; R_0603_1608Metric; MPN RC0603FR-103KL

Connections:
+5V: R37.1, R40.1, R43.1; also elsewhere on the board
/E_STOP_COM: Q1.1 (G), R38.1, R39.1; also elsewhere on the board
/E_STOP_R_OUT: Q2.1 (G), R41.1, R42.1; also elsewhere on the board
/HVIL_OUT: Q3.1 (G), R44.1, R46.1; also elsewhere on the board
/SS_ESTOP_L: Q1.3 (D), R37.2; also elsewhere on the board
/SS_ESTOP_R: Q2.3 (D), R40.2; also elsewhere on the board
/SS_MC: Q3.3 (D), R43.2; also elsewhere on the board
GND: Q1.2 (S), Q2.2 (S), Q3.2 (S); also elsewhere on the board
unnamed: D31.2 (A), R39.2
unnamed: D31.1 (K), R38.2
unnamed: D32.2 (A), R42.2
unnamed: D32.1 (K), R41.2
unnamed: D33.2 (A), R46.2
unnamed: D33.1 (K), R44.2

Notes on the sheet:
E_STOP_R to MCU
E_STOP_COM to MCU
HVIL to MCU

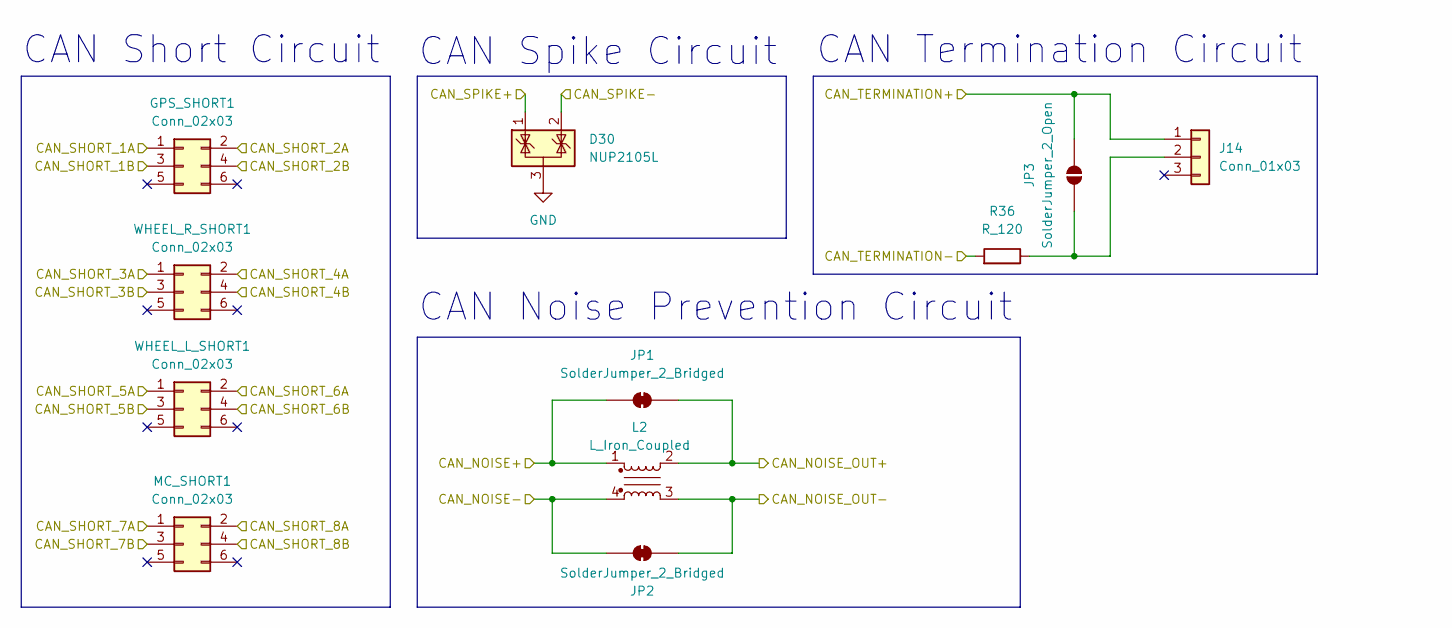
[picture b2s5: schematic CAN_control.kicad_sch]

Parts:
D30: NUP2105L; SOT-23
GPS_SHORT1: Conn_02x03; PinHeader_2x03_P2.54mm_Vertical
J14: Conn_01x03; PinHeader_1x03_P2.54mm_Vertical
JP1, JP2: SolderJumper_2_Bridged; SolderJumper-2_P1.3mm_Bridged2Bar_Pad1.0x1.5mm
JP3: SolderJumper_2_Open; SolderJumper-2_P1.3mm_Open_Pad1.0x1.5mm
L2: L_Iron_Coupled; L_CommonModeChoke_Coilcraft_1812CAN
MC_SHORT1: Conn_02x03; PinHeader_2x03_P2.54mm_Vertical
R36: R_120; R_0603_1608Metric; MPN RC0603FR-13120RL
WHEEL_L_SHORT1: Conn_02x03; PinHeader_2x03_P2.54mm_Vertical
WHEEL_R_SHORT1: Conn_02x03; PinHeader_2x03_P2.54mm_Vertical

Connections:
/CAN_1+: GPS_SHORT1.1, J14.1, JP3.1 (A); also elsewhere on the board
/CAN_1-: GPS_SHORT1.2, R36.2; also elsewhere on the board
/CAN_2+: GPS_SHORT1.3, WHEEL_R_SHORT1.1; also elsewhere on the board
/CAN_2-: GPS_SHORT1.4, WHEEL_R_SHORT1.2; also elsewhere on the board
/CAN_3+: WHEEL_L_SHORT1.1, WHEEL_R_SHORT1.3; also elsewhere on the board
/CAN_3-: WHEEL_L_SHORT1.2, WHEEL_R_SHORT1.4; also elsewhere on the board
/CAN_4+: MC_SHORT1.4, WHEEL_L_SHORT1.3; also elsewhere on the board
/CAN_4-: MC_SHORT1.3, WHEEL_L_SHORT1.4; also elsewhere on the board
/CAN_5+: D30.1 (K), JP1.2 (B), L2.2, MC_SHORT1.1; also elsewhere on the board
/CAN_5-: D30.2 (K), JP2.1 (A), L2.3, MC_SHORT1.2; also elsewhere on the board
/CAN_6+: JP1.1 (A), L2.1; also elsewhere on the board
/CAN_6-: JP2.2 (B), L2.4; also elsewhere on the board
GND: D30.3 (A); also elsewhere on the board
unnamed: J14.2, JP3.2 (B), R36.1

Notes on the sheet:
CAN Noise Prevention Circuit
CAN Spike Circuit
CAN Termination Circuit
CAN Short Circuit
